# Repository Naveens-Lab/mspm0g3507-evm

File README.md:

# MSPM0G3507 Dev Board — EVM-Style Hardware Platform

> *An embedded software engineer's journey into hardware design.*

---

## Overview

A custom EVM (Evaluation Module) style development board built around the **TI MSPM0G3507** microcontroller. The project started as a personal deep-dive into schematic and PCB design  something I had always wanted to do coming from an embedded software background and has grown into a platform I intend to keep expanding.

The board includes a **Microchip ATECC608A** hardware secure element, making it suitable for exploring hardware-backed cryptography, device authentication, and secure key storage on a board I designed myself. Beyond the learning aspect, I plan to build real applications here: IoT device authentication, secure bootloader prototyping, and more.

---

## Schematic

---

## PCB — REV A

---

## Hardware — Bill of Materials

| Ref | Part | Description |
|---|---|---|
| U2 | **TI MSPM0G3507SPTR** | 32-bit Arm Cortex-M0+, 80MHz, 128KB Flash, LQFP-64 |
| U3 | **Microchip ATECC608A-SSHDA** | Hardware secure element — ECC, SHA-256, I2C interface |
| U1 | **SPX3819M5-L-3-3** | 3.3V LDO voltage regulator |
| U4 | **USBLC6-2SC6** | USB line ESD protection (bidirectional TVS) |
| U5 | **CH340E** | USB-to-UART bridge IC |
| J1 | **USB-C Receptacle** | USB 2.0, 16P — power input + UART comms |
| J2 | **TC2030 (Tag-Connect)** | SWD debug/programming header — no connector bulk |
| X1 | **8 MHz Crystal** | High-frequency external oscillator (HFXT) |
| R2, R3 | 5.1kΩ | I2C pull-ups for ATECC608A (SCL / SDA) |
| R5, R6 | 5.1kΩ | USB-C CC1 / CC2 pull-downs (UFP/sink mode) |

---

## Connectivity

```
                    +3V3
                     │
  USB-C ─► USBLC6 ─► CH340E ──(UART0: PA0/PA1)──► MSPM0G3507SPTR
                              │                         │
                       UD+/UD-│                    I2C0 (PA10/PA11)
                              │                         │
                         (USB FS)                  ATECC608A-SSHDA
                                                   (Secure Element)

  SWD ─► TC2030 ──(SWDIO: PA19 / SWCLK: PA20)──► MSPM0G3507SPTR

  VBUS ─► SPX3819M5-L-3-3 (LDO) ─► +3V3 (board rail)
```

---

## Design Goals

- **EVM-style** — clean layout, labeled, easy to probe; breakout headers for GPIO access
- **Minimal but complete** — everything needed to get code running, nothing unnecessary
- **Secure element first-class** — ATECC608A on dedicated I2C0 bus with proper pull-ups and decoupling
- **Debug-friendly** — TC2030 Tag-Connect for SWD; no bulky 10-pin IDC connector needed
- **USB-C native** — power and UART over a single cable; USBLC6 ESD protection on data lines
- **Expandable** — designed with future revisions in mind; more peripherals and features planned

---

## Roadmap

- [x] MCU schematic — MSPM0G3507SPTR (LQFP-64)
- [x] ATECC608A-SSHDA secure element circuit (I2C0)
- [x] USB-C + USBLC6 ESD + CH340E UART bridge
- [x] SPX3819M5-L-3-3 3.3V LDO power circuit
- [x] TC2030 SWD debug header
- [x] 8 MHz HFXT crystal circuit
- [x] PCB layout — REV A (in progress, pre-fab)
- [x] DRC clean pass + design review
- [ ] Gerber generation and PCB fabrication
- [ ] Board bring-up firmware (MSPM0 DriverLib, bare-metal)
- [ ] ATECC608A I2C driver + device wake-up sequence
- [ ] ATECC608A provisioning (TrustFLEX / TrustCustom configuration)
- [ ] Hardware-backed device authentication demo (ECC challenge-response)
- [ ] Secure bootloader prototype using ATECC608A key storage
- [ ] USB CDC firmware (v2 — remove CH340E dependency)
- [ ] QSPI external flash (future revision)
- [ ] OLED / e-ink display header (future revision)

---

## Tools

- **KiCad 9.0** — Schematic capture and PCB layout
- **TI MSPM0G3507 Datasheet + TRM** — MCU peripheral and pin configuration reference
- **TI MSPM0 SDK / DriverLib** — Firmware development
- **Microchip ATECC608A Datasheet + CryptoAuthLib** — Secure element integration reference

---

## Repository Structure

```
mspm0g3507-evm/
├── assets/
│   ├── schematic.png                        # Schematic export
│   └── pcb_3d_top.png                       # PCB 3D render — REV A
├── kicad/
│   ├── MSPM0_DevBoard.kicad_pro
│   ├── MSPM0_DevBoard.kicad_sch
│   ├── MSPM0_DevBoard.kicad_pcb
│   └── MSPM0G3507_Sym_Symbl.kicad_sym       # Custom MCU symbol library
├── datasheets/                               # MSPM0G3507, ATECC608A, CH340E, SPX3819
├── gerbers/                                  # Generated at fab-ready milestone
├── firmware/                                 # Bring-up and demo firmware
└── README.md
```

---

## Why This Project?

I have spent 6+ years as an embedded software engineer  writing firmware for automotive EV , elevator controllers, medical devices, and defense systems. I have always worked *on top of* hardware that someone else designed. This project is me crossing that line: learning how the schematic becomes a PCB, how a PCB becomes a product, and how every decision made during layout shows up as a bug (or not) at bring-up.

The ATECC608A is here because hardware-backed security is something I want to understand deeply not just at the register level from firmware, but from the moment the footprint lands on the board.

This is REV A. It will not be perfect. That is the point.

---

## License

Hardware design files (schematic, PCB) licensed under [CERN Open Hardware Licence v2 - Permissive (CERN-OHL-P)](https://ohwr.org/cern_ohl_p_v2.txt).  
Firmware  licensed under MIT.

---

## Author

**Naveen** — Embedded Systems Engineer  
Firmware architecture ·Hardware-firmware integration  
Automotive · Industrial · Power Electronics

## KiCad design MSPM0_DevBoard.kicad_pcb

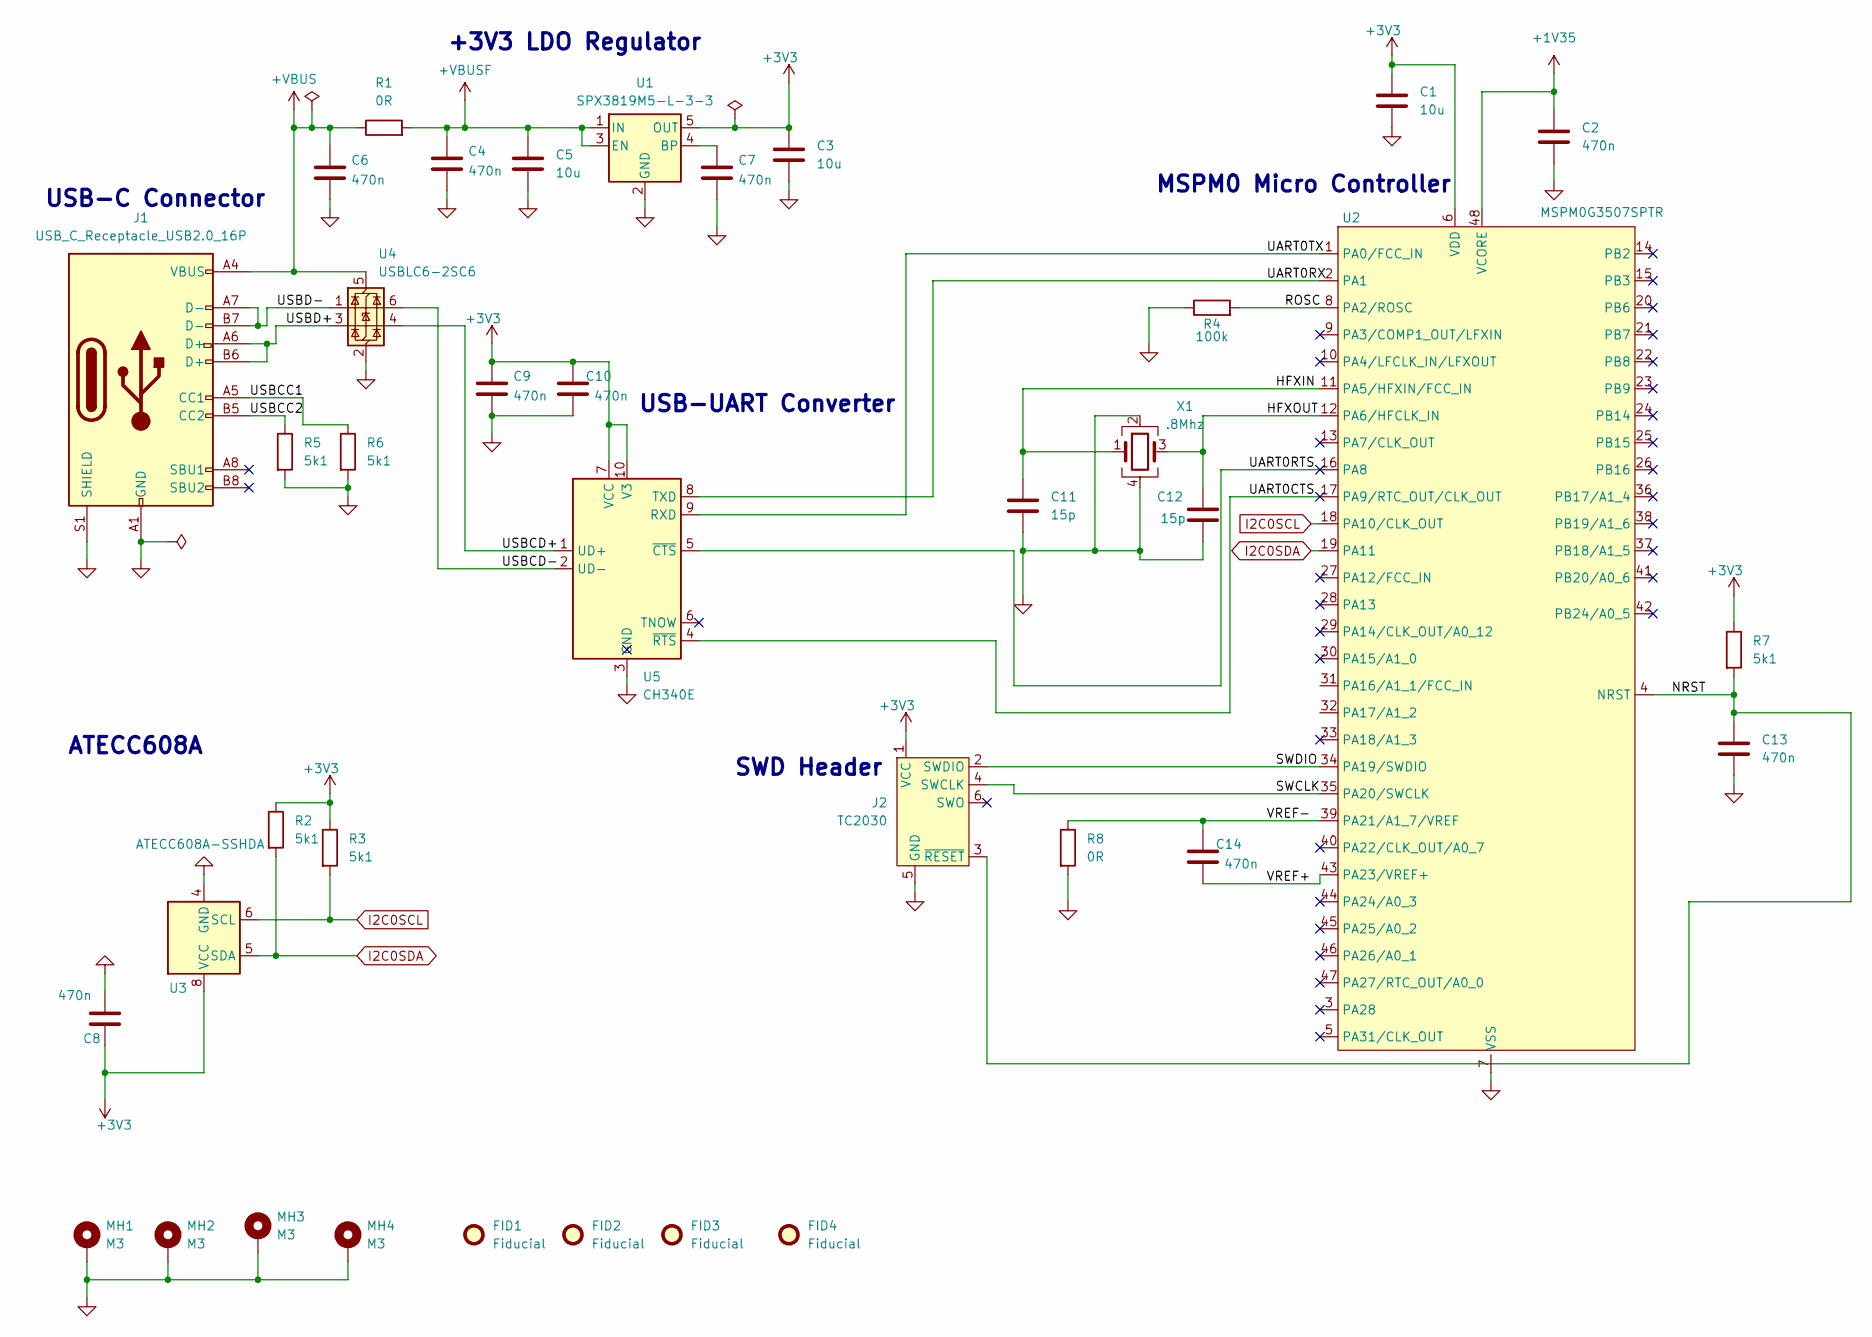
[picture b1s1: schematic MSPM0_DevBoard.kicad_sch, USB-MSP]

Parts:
C1, C3, C5: 10u; C_0805_2012Metric; Manufacturer Part Number CL21A106KAYNNNE; LCSC C15850
C2, C4, C6, C7, C8, C9, C10, C13, C14: 470n; C_0805_2012Metric; Manufacturer Part Number CL21B474KBFNNNE; LCSC C13967
C11, C12: 15p; C_0805_2012Metric; Manufacturer Part Number CL21B474KBFNNNE; LCSC C13967
FID1, FID2, FID3, FID4: Fiducial; Fiducial_1mm_Mask2mm
J1: USB_C_Receptacle_USB2.0_16P; USB_C_Receptacle_GCT_USB4105-xx-A_16P_TopMnt_Horizontal
J2: TC2030; Tag-Connect_TC2030-IDC-FP_2x03_P1.27mm_Vertical
MH1, MH2, MH3, MH4: M3; MountingHole_3.2mm_M3_Pad_Via
R1, R8: 0R; R_0603_1608Metric
R2, R3, R5, R6, R7: 5k1; R_0603_1608Metric
R4: 100k; R_0201_0603Metric; Manufacter Partnumber RT73F1J100KBTD
U1: SPX3819M5-L-3-3; SOT-23-5
U2: MSPM0G3507SPTR; LQFP-48_7x7mm_P0.5mm; Manufacturer Part Number MSPM0G3507SPTR; LCSC C22362630
U3: ATECC608A-SSHDA; SOIC-8_3.9x4.9mm_P1.27mm
U4: USBLC6-2SC6; SOT-23-6
U5: CH340E; MSOP-10_3x3mm_P0.5mm
X1: .8Mhz; Crystal_SMD_3225-4Pin_3.2x2.5mm

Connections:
+1V35: C2.1, U2.48 (VCORE)
+3V3: C1.1, C3.1, C8.1, C9.2, C10.2, J2.1 (VCC), R2.1, R3.1, R7.1, U1.5 (OUT), U2.6 (VDD), U3.8 (VCC), U5.7 (VCC), U5.10 (V3)
+VBUS: C6.2, J1.A4 (VBUS), J1.A9 (VBUS), J1.B4 (VBUS), J1.B9 (VBUS), R1.1, U4.5 (VBUS)
+VBUSF: C4.2, C5.1, R1.2, U1.1 (IN), U1.3 (EN)
/HFXIN: C11.1, U2.11 (PA5/HFXIN/FCC_IN), X1.1
/HFXOUT: C12.1, U2.12 (PA6/HFCLK_IN), X1.3
/NRST: C13.1, J2.3 (~RESET), R7.2, U2.4 (NRST)
/ROSC: R4.2, U2.8 (PA2/ROSC)
/SWCLK: J2.4 (SWCLK), U2.35 (PA20/SWCLK)
/SWDIO: J2.2 (SWDIO), U2.34 (PA19/SWDIO)
/UART0CTS: U2.17 (PA9/RTC_OUT/CLK_OUT), U5.4 (~RTS)
/UART0RTS: U2.16 (PA8), U5.5 (~CTS)
/UART0RX: U2.2 (PA1), U5.8 (TXD)
/UART0TX: U2.1 (PA0/FCC_IN), U5.9 (RXD)
/USBCC1: J1.A5 (CC1), R6.1
/USBCC2: J1.B5 (CC2), R5.1
/USBCD+: U4.4 (I/O2), U5.1 (UD+)
/USBCD-: U4.6 (I/O1), U5.2 (UD-)
/USBD+: J1.A6 (D+), J1.B6 (D+), U4.3 (I/O2)
/USBD-: J1.A7 (D-), J1.B7 (D-), U4.1 (I/O1)
/VREF+: C14.1, U2.43 (PA23/VREF+)
/VREF-: C14.2, R8.1, U2.39 (PA21/A1_7/VREF)
GND: C1.2, C2.2, C3.2, C4.1, C5.2, C6.1, C7.1, C8.2, C9.1, C10.1, C11.2, C12.2, C13.2, J1.A1 (GND), J1.A12 (GND), J1.B1 (GND), J1.B12 (GND), J1.S1 (SHIELD), J2.5 (GND), MH1.1, MH2.1, MH3.1, MH4.1, R4.1, R5.2, R6.2, R8.2, U1.2 (GND), U2.7 (VSS), U3.4 (GND), U4.2 (GND), U5.3 (GND), X1.2, X1.4
I2C0SCL: R3.2, U2.18 (PA10/CLK_OUT), U3.6 (SCL)
I2C0SDA: R2.2, U2.19 (PA11), U3.5 (SDA)
unnamed: C7.2, U1.4 (BP)

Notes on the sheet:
USB-UART Converter
ATECC608A
USB-C Connector
SWD Header
+3V3 LDO Regulator
MSPM0 Micro Controller

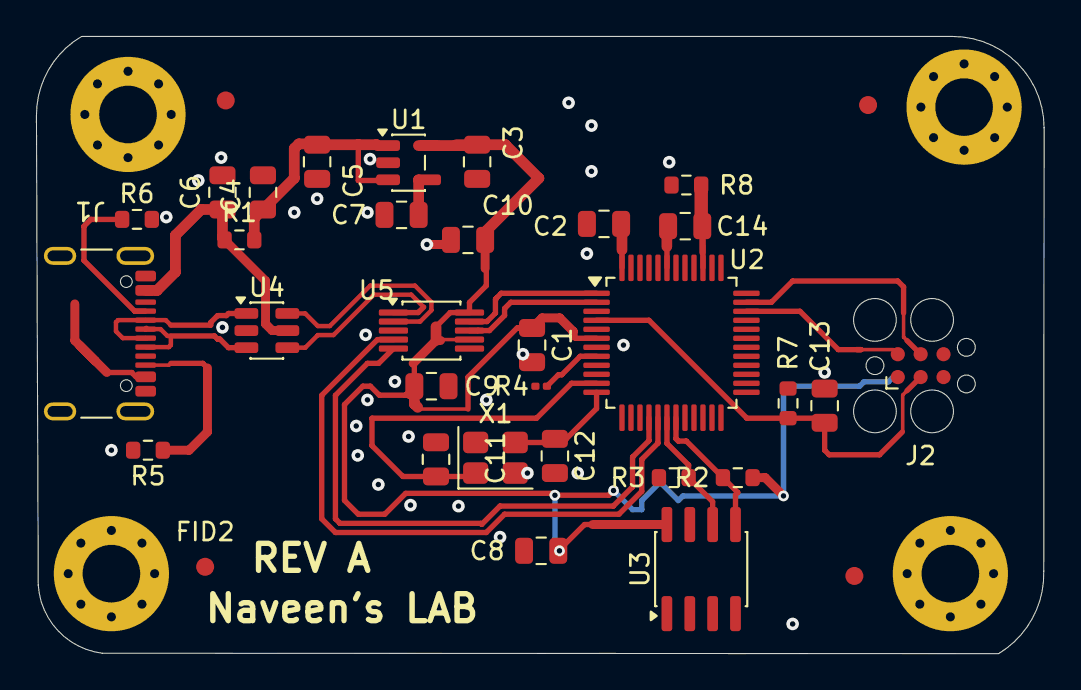
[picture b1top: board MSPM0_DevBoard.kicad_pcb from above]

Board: 2 copper layers, 56.0 x 34.3 mm, 38 parts (0 on the bottom side), 26 nets.

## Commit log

2026-06-09 Adding Kicad Project files
